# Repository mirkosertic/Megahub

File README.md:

# Megahub

## Introduction

Megahub is an ESP32-based experimentation platform for robotics enthusiasts and makers. It combines native support for LEGO WeDo/Powered Up devices with a web-based IDE featuring Lua scripting and Blockly visual programming. The project is fully open source and ships with hardware schematics, PCB production files, and firmware as a PlatformIO project.

**Build and use it at your own risk.**

---

## Key Features

- **KiCad schematics**: All schematics and PCB production files are available in KiCad and Gerber format
- **WiFi**: Built-in wireless connectivity for remote control and programming
- **Bluetooth**: Acts as a BLE (Bluetooth Low Energy) server and Bluetooth Classic client simultaneously
- **Web IDE**: Configure and program Megahub through the [Megahub IDE](https://mirkosertic.github.io/Megahub/)
- **Visual programming**: Blockly drag-and-drop programming for beginners and rapid prototyping
- **Lua scripting**: Full Lua 5.4 scripting for advanced users
- **SD card storage**: Store multiple projects on an SD card; the IDE remembers which project was last selected for autostart
- **4 LEGO device ports**: Connect up to 4 LEGO WeDo 2.0/Powered Up motors, sensors, and other devices simultaneously
- **IMU**: Integrated MPU6050 6-axis accelerometer and gyroscope for motion sensing
- **FastLED/NeoPixel**: Built-in support for WS2812B addressable RGB LED strips
- **GPIO expansion**: Additional GPIO pins for custom sensors, buttons, and peripherals
- **Gamepad support**: Pair a Bluetooth Classic HID gamepad (e.g., 8BitDo M30) for manual control

---

## Screenshots

**Project management**

**IMU interaction**

**LEGO and Gamepad interaction**

---

## Hardware Photos

---

## Getting Started

### Prerequisites

- [PlatformIO](https://platformio.org/) installed as a CLI tool or as a VSCode extension
- An ESP32 development board
- USB cable for flashing
- Chrome, Edge, or Opera desktop browser (required for the Web Bluetooth API)

### Building the Firmware

1. Clone the repository:
   ```bash
   git clone https://github.com/mirkosertic/Megahub.git
   cd Megahub
   ```

2. Build the project:
   ```bash
   pio run
   ```
   Or click **Build** in the PlatformIO toolbar inside VSCode.

### Flashing the Board

1. Connect the ESP32 board via USB.

2. Flash the firmware:
   ```bash
   pio run --target upload
   ```
   Or click **Upload** in the PlatformIO toolbar inside VSCode.

### First Boot and Connection

The device starts in **Bluetooth mode** by default.

1. Open the [Megahub IDE](https://mirkosertic.github.io/Megahub/) in Chrome, Edge, or Opera on a desktop computer.
2. Click **Connect** in the IDE.
3. Select your Megahub device from the browser's Bluetooth pairing dialog.
4. Once connected, the IDE shows the project list and the logger output.

### Serial Monitor

View diagnostic output from the board:
```bash
pio device monitor
```
Default baud rate: **115200**.

### Testing the IDE Without Hardware

You can run the Megahub IDE locally in your browser without a physical board. This is useful for exploring the interface, building Blockly programs, and inspecting generated Lua code — no firmware flashing required.

```bash
cd frontend
npm install
npm run dev
```

Vite starts a local development server (typically at `http://localhost:5173`). Open that URL in any browser.

**What works in dev mode:**
- Full IDE UI — project management, Blockly workspace, toolbox
- Blockly drag-and-drop programming and real-time Lua code generation
- Lua Preview panel — inspect the generated code for any program

**What does not work:**
- Connecting to a device (no BLE in dev mode)
- Executing or stopping programs — the **Execute** button requires a live connection to the firmware

---

## Hardware Reference

### LEGO Device Ports

Megahub provides **4 LEGO device ports**, numbered **1 to 4**. Each port uses the LEGO Powered Up UART protocol. Two SC16IS752 I2C-to-UART bridge chips translate between the ESP32 and the LEGO connectors: **bridge chip 1** (UART1) drives ports 1 and 2, **bridge chip 2** (UART2) drives ports 3 and 4. Each chip also exposes four additional GPIO pins (GP4–GP7) that can be used for custom sensors or buttons — see `UART1_GP4`–`UART2_GP7` in [LUAAPI.md](LUAAPI.md). All four ports are available from Blockly.

Motor speed range: **-127** (full reverse) to **+127** (full forward). Zero stops the motor.

### GPIO Pins

**FastLED / NeoPixel output** — use any of these GPIO pins for WS2812B LED strips: **13, 16, 17, 25, 26, 27, 32, 33**.

**SD card (SPI bus)**:

| Signal | GPIO |
|--------|------|
| CLK    | 18   |
| MOSI   | 23   |
| MISO   | 19   |
| CS     | 4    |

**IMU (I2C)**: The MPU6050 is connected to the I2C bus. Its address and pins are fixed in hardware.

### Supported LEGO Devices

Megahub supports LEGO WeDo 2.0 and Powered Up devices that communicate over the LEGO Powered Up UART (LUMP) protocol. This includes motors, color and distance sensors, tilt sensors, and other compatible devices. See the [LUMP Protocol Documentation](LUMP.md) for the full technical specification.

---

## Using the IDE

### Connecting

The [Megahub IDE](https://mirkosertic.github.io/Megahub/) runs entirely in your browser and communicates over BLE when the device is in Bluetooth mode.

**Supported browsers**: Chrome, Edge, Opera (desktop only). Firefox and Safari do not support the Web Bluetooth API and cannot connect to the device.

Steps:
1. Open the IDE in a supported browser.
2. Click **Connect**.
3. Select the Megahub device from the pairing dialog.
4. The IDE connects and shows the project list on the left and a logger panel on the right.

### Creating a Project

1. Click **New project** in the project list.
2. Enter a name for the project.
3. The IDE opens the Blockly workspace for that project.

### Programming with Blockly

The Blockly workspace lets you build programs visually without writing code.

1. Find a block in the **toolbox** on the left side of the workspace. Blocks are grouped by category: Control flow, LEGO, Gamepad, FastLED, IMU, I/O, Math, and more.
2. Drag a block onto the canvas and connect it to other blocks.
3. As you build, the IDE generates the corresponding Lua code automatically — expand the **Lua Preview** panel in the sidebar to inspect it.
4. When the program is ready, click **Execute** to send and run it on the device.
5. Output and log messages from the running program appear in the **Logger** panel.

For a visual reference of every available block, see [BLOCKS.md](BLOCKS.md).

### Toolbox Category Guide

The toolbox is divided into these categories:

| Category | What it contains |
|----------|-----------------|
| **Control flow** | `Initialization` block, `Start thread`, `Wait`, `Stop thread` |
| **Logic** | If/else, comparisons (=, ≠, <, >), AND/OR, NOT, boolean values |
| **Loop** | Repeat N times, count-for loop, break/continue |
| **Math** | Arithmetic, rounding, trigonometry, random numbers, constrain |
| **Text** | String operations; **Print to Logger** |
| **Lists** | Create, read, write, sort, and split lists |
| **I/O** | **Set motor speed**, GPIO read/write, pin mode, port selector |
| **LEGO©** | Select sensor mode on a port, read sensor dataset |
| **Gamepad** | Button pressed, analog axis values, connection check |
| **FastLED** | Initialize LED strip, set individual LED colour, show, clear |
| **IMU** | Read yaw, pitch, roll, or acceleration from the on-board sensor |
| **UI** | Display a labelled value in the IDE Logger panel, map visualization (plot position, clear) |
| **Algorithms** | PID controller (init/compute/reset), dead reckoning (init/update/get/reset/set pose), moving average filter, map/scale, hysteresis, debounce, rate limiter, 1D Kalman filter |
| **Debug** | Free heap memory, milliseconds since boot |

> **Common gotcha:** The **Set motor speed** block is in the **I/O** category — not **LEGO©**. The **LEGO©** category only contains sensor blocks (selecting a measurement mode and reading the sensor dataset). If you want to drive a motor, open **I/O**.

### Running and Stopping Programs

- Click **Execute** to upload and start the program.
- Click **Stop** to halt a running program at any time.
- The Logger panel shows output in real time.

### Autostart

You can mark a project as the autostart project. When the IDE connects to the device, it reads the autostart setting and opens that project automatically.

In the IDE project list, find the project you want and toggle the **autostart** switch. This writes the following file to the SD card:

```json
{ "project": "your-project-id" }
```

The file is stored at `/autostart.json` on the SD card. To clear the autostart selection, toggle the switch off in the IDE or delete the file from the SD card.

---

## WiFi Mode

By default Megahub runs in Bluetooth mode. You can switch to WiFi mode to access the web interface over your local network.

### Switching from Bluetooth to WiFi Mode

1. Insert an SD card into the device.
2. Create a file named `config.json` in the root of the SD card with the following content:
   ```json
   {
     "bluetoothEnabled": false,
     "wifiEnabled": true,
     "ssid": "YourNetwork",
     "pwd": "YourPassword"
   }
   ```
3. Reboot the device. It connects to your WiFi network and starts the web server.

You can also run both Bluetooth and WiFi simultaneously by setting both `bluetoothEnabled` and `wifiEnabled` to `true`.

### config.json Reference

| Field              | Type    | Default | Description                        |
|--------------------|---------|---------|------------------------------------|
| `bluetoothEnabled` | boolean | `true`  | Enable BLE and Bluetooth Classic   |
| `wifiEnabled`      | boolean | `false` | Connect to WiFi and start web server |
| `ssid`             | string  | —       | WiFi network name                  |
| `pwd`              | string  | —       | WiFi password                      |

### Accessing the Web UI

Once the device is connected to WiFi:
- Open `http://<device-ip>/` in any browser, **or**
- Open `http://<device-uid>.local/` (requires mDNS support — works on macOS, Linux, and Windows 10+)

The web UI provides the same project management, Blockly programming, and execution features as the Bluetooth-connected IDE. For the full REST API reference used by the web server, see [HUBAPI.md](HUBAPI.md).

---

## Gamepad Support

### Pairing a Gamepad

Scanning and pairing are done from the IDE while the device is connected in Bluetooth mode.

1. Open the **Bluetooth Devices** panel in the IDE sidebar.
2. Click the **Scan** button (circular icon at the top of the panel). The panel shows "Scanning…" while the firmware searches for nearby Bluetooth Classic devices.
3. Put your gamepad into pairing mode so it becomes discoverable.
4. The gamepad appears in the list with its name, MAC address, device type, and signal strength.
5. Click **Pair Device** on the gamepad entry. The firmware initiates pairing; the entry updates to show a **Paired** badge.
6. Once paired, the gamepad state is available to your Blockly programs immediately.

To remove a pairing, click **Remove Pairing** on the paired device entry in the panel.

### Supported Gamepads

Any Bluetooth Classic HID-compatible gamepad should work. The **8BitDo M30** has been tested and confirmed to work.

Gamepad input available in Blockly:

| Input           | Range / Values              |
|-----------------|-----------------------------|
| Buttons (1–16)  | pressed / not pressed       |
| D-pad           | directional state           |
| Left stick X/Y  | -32768 to +32767            |
| Right stick X/Y | -32768 to +32767            |

### Blockly Blocks for Gamepad

The **Gamepad** category in the Blockly toolbox provides 5 blocks for reading button states, D-pad direction, and analog stick values. See [BLOCKS.md](BLOCKS.md) for the full visual reference.

---

## Hardware Features

### LEGO Powered Up

Megahub speaks the LEGO Powered Up UART protocol (LUMP) natively. Each of the 4 ports independently detects a connected device, negotiates its capabilities, and streams sensor data. Motors accept a speed value from -127 to +127. Sensors report values according to the mode you select in your Blockly program.

The **LEGO** category in the Blockly toolbox provides blocks for:
- Selecting a sensor mode on a port
- Reading the current sensor data from a port and dataset

Motor speed is set using the **Set motor speed** block in the **I/O** category.

See [LUMP.md](LUMP.md) for the complete protocol specification.

### FastLED / NeoPixel Addressable LEDs

Connect a WS2812B LED strip to any of the supported GPIO pins (13, 16, 17, 25, 26, 27, 32, or 33). The **FastLED** category in the Blockly toolbox provides 4 blocks for:
- Initializing the LED strip (type, GPIO pin, number of LEDs)
- Setting individual LED colors (RGB)
- Showing/updating the LED strip
- Clearing all LEDs

### IMU — Orientation and Acceleration

The on-board MPU6050 provides 6-axis motion data, updated every 100 ms. Read it in Blockly using the **IMU** block:

| Output          | Unit  | Description                    |
|-----------------|-------|--------------------------------|
| YAW             | °     | Rotation around vertical axis  |
| PITCH           | °     | Forward/back tilt              |
| ROLL            | °     | Left/right tilt                |
| ACCELERATION_X  | m/s²  | Acceleration along X axis      |
| ACCELERATION_Y  | m/s²  | Acceleration along Y axis      |
| ACCELERATION_Z  | m/s²  | Acceleration along Z axis      |

### Algorithm Blocks

The **Algorithms** category provides blocks for closed-loop control and position tracking.

**PID controller:** A proportional-integral-derivative controller for motor speed regulation, line following, or any closed-loop control. Uses an explicit lifecycle:
1. **Init PID** — creates a new controller instance, returns a handle
2. **PID compute** — computes control output using the handle, setpoint, process variable, and gains
3. **PID reset** — clears the state of an existing controller (e.g., when switching setpoints)

Store the handle from `Init PID` in a variable and pass it to `PID compute` in your control loop.

**Dead reckoning (DR):** Estimates the robot's (x, y, heading) pose by integrating wheel encoder ticks and IMU yaw. The following blocks are available:

| Block | Description |
|-------|-------------|
| `Init DR` | Creates a new dead reckoning instance and returns a handle. Call once before your main loop. |
| `DR update` | Updates pose from left/right encoder ticks and IMU yaw. Takes 7 inputs: handle, left ticks, right ticks, yaw (deg), m/tick, wheelbase (m), IMU weight. Does not return a value. |
| `DR pose X/Y/HEADING of` | Reads one component of the pose from a handle — X and Y in meters, HEADING in degrees. |
| `Reset DR pose of` | Resets pose to origin (0, 0, 0°). Re-bootstraps encoder baselines so the next update produces zero delta. |
| `Set DR pose of` | Injects a known (x, y, heading) position for landmark-based drift correction. |

**Moving average filter:** Smooths noisy sensor readings using a sliding window of the last N samples. Uses the same explicit handle pattern as PID and DR — call `Initialize moving average` once before your loop, store the handle in a variable, then pass it to `Moving average` on each update.

| Block | Description |
|-------|-------------|
| `Initialize moving average` | Creates a new moving average filter instance and returns a handle. Store in a variable. Call once before your loop. |
| `Moving average` | Adds a new sample and returns the arithmetic mean of the last N values. Inputs: handle, sensor value, window size (2–50; default 10). On first call the buffer is pre-filled so there is no startup ramp. |

**Map / Scale:** Linearly maps a value from one numeric range to another. Stateless — no initialization required.

| Block | Description |
|-------|-------------|
| `Map` | Maps `value` from `[inMin, inMax]` to `[outMin, outMax]`. Equivalent to Arduino `map()` with float support. Output is not clamped — values outside the input range extrapolate linearly. |

**LEGO motor POS mode prerequisite:** DR reads absolute encoder positions. Before using DR blocks, call `lego select mode` with mode **2** (POS) on the motor ports in `hub.init()`, then wait briefly for the sensor to settle.

For a full explanation including the math, calibration procedure, coordinate conventions, and example programs, see [DEADRECKONING.md](DEADRECKONING.md).

**Signal conditioning filters:** Four filters for cleaning up noisy or jerky signals before they reach your control logic. All use the same explicit handle pattern as PID and DR.

| Block pair | Description |
|-----------|-------------|
| `Initialize hysteresis` + `Hysteresis` | Schmitt trigger — output latches to 0 or 1, only switching when the input crosses a high or low threshold. Eliminates chatter at sensor boundaries. |
| `Initialize debounce` + `Debounce` | Waits for a digital signal to be stable for a minimum number of milliseconds before updating output. Eliminates mechanical button bounce and contact noise. |
| `Initialize rate limiter` + `Rate limit` | Limits how fast the output value can change per call, producing smooth acceleration ramps. Prevents wheel slip and encoder errors from sudden motor commands. |
| `Initialize Kalman filter` + `Kalman filter` | 1D Kalman filter — weighted sensor smoothing based on process noise Q and measurement noise R. More principled than moving average for sensors with known noise characteristics. |

For intuition, math, tuning guidance, and pipeline examples, see [FILTERS.md](FILTERS.md).

### Map Visualization

The IDE sidebar includes a **live map panel** that renders the robot's trail as it moves. Use the **UI** category blocks to drive it:

| Block | Description |
|-------|-------------|
| `Map: plot position` | Sends an (x, y, heading) pose to the map panel. Wire in DR get blocks for x, y, and heading. The firmware rate-limits sends to 5 Hz — call at any rate in your loop. |
| `Map: clear` | Clears the trail from the map panel. Call this at the start of each run alongside `Reset DR pose`. |

### SD Card Storage

Projects created in the IDE are saved to the SD card. The SD card connects over SPI (CLK=18, MOSI=23, MISO=19, CS=4). Use a standard microSD card formatted as FAT32. Configuration files (`config.json`, `autostart.json`) also live in the root of the SD card.

**SD card is required.** If the SD card is absent or fails to mount at boot, the device halts immediately and cannot start.

---

## How Programs Run

Understanding this sequence explains many "why isn't it working?" situations.

### Boot sequence

1. The SD card is mounted. **If mounting fails the device halts** — nothing else starts.
2. `config.json` is read from the SD card root. WiFi and/or Bluetooth are started based on its content.
3. All four LEGO ports initialise and begin device detection in the background.
4. The device enters idle state. No program runs automatically at this point.

> **Autostart does not run a program at boot.** The autostart setting only tells the IDE which project to navigate to when you connect. The device always starts with no program running — you must click **Execute** in the IDE to start a program.

### When you click Execute

1. Any currently running program and all its threads are **stopped immediately**.
2. All four LEGO ports are **reinitialized** (motors stop, sensors reset).
3. A fresh Lua environment is created and the program runs from the top:
   - `hub.init()` — runs synchronously and completes before anything else.
   - `hub.startthread()` — each call spawns a background task that loops independently.
   - The main program body finishes. Background threads continue running.
4. Each thread loops continuously with a 1 ms scheduler yield between iterations.

### When a thread crashes

If a Lua runtime error occurs inside a thread:

- The thread exits and the error appears in the **Logger** panel.
- All four LEGO ports are reinitialized (all motors stop).
- Other threads continue running.

### When you click Stop

1. All threads receive a stop signal and exit.
2. All four LEGO ports are reinitialized (all motors stop, all sensors reset).

**Key point:** every time a program stops — by request, by crashing, or because a new Execute is sent — all motors stop and all ports reset. You never need to manually zero motors before stopping.

---

## Troubleshooting

### BLE Not Connecting

- Make sure you are using Chrome, Edge, or Opera on a **desktop** computer. Mobile browsers and Firefox/Safari do not support the Web Bluetooth API.
- Ensure Bluetooth is enabled on your computer.
- Reload the IDE page and click Connect again — the browser may need a fresh connection attempt.
- Check that no other browser tab or application is already connected to the device (only one BLE connection is active at a time).

### Device Not Found in Bluetooth Scan

- Confirm the device is powered on.
- Move the device closer to your computer — BLE range is typically 5–10 metres in open air.
- Reboot the device and try the scan again.
- If the device was previously paired with a different computer, you may need to remove it from that computer's Bluetooth settings first.

### LEGO Device Not Responding

- Check that the LEGO device cable is fully seated in the port.
- Confirm the port number in your Blockly program matches the physical port (1–4).
- Some LEGO devices require a short delay between commands. Add a **wait** block between motor commands if the device ignores rapid successive commands.
- Reboot the device. The port detection sequence runs on every startup.

### Reading the Serial Log

Connect the device via USB and run:
```bash
pio device monitor
```
The log (115200 baud) shows boot messages, port detection results, BLE connection events, and any errors from running Lua programs. Copy the relevant lines when reporting a bug.

---

## Documentation

| Document | Description |
|----------|-------------|
| [BLOCKS.md](BLOCKS.md) | Complete visual reference for all Blockly blocks, auto-generated with screenshots |
| [LUAAPI.md](LUAAPI.md) | Lua scripting API — all modules, functions, and constants available in Megahub programs |
| [BLEPROTOCOL.md](BLEPROTOCOL.md) | BLE protocol reference — GATT profile, framing, request/response and event formats |
| [HUBAPI.md](HUBAPI.md) | REST API and Server-Sent Events reference for WiFi mode |
| [LUMP.md](LUMP.md) | LEGO Powered Up UART protocol technical specification |
| [MEGAHUBIDE.md](MEGAHUBIDE.md) | Frontend IDE architecture — module structure, state, events, components, testing |
| [DEADRECKONING.md](DEADRECKONING.md) | Dead reckoning guide — intuition, kinematics, math, coordinate conventions, Blockly usage, and calibration |
| [FILTERS.md](FILTERS.md) | Signal conditioning filters guide — hysteresis, debounce, rate limiter, and 1D Kalman filter: intuition, math, tuning, and pipeline patterns |

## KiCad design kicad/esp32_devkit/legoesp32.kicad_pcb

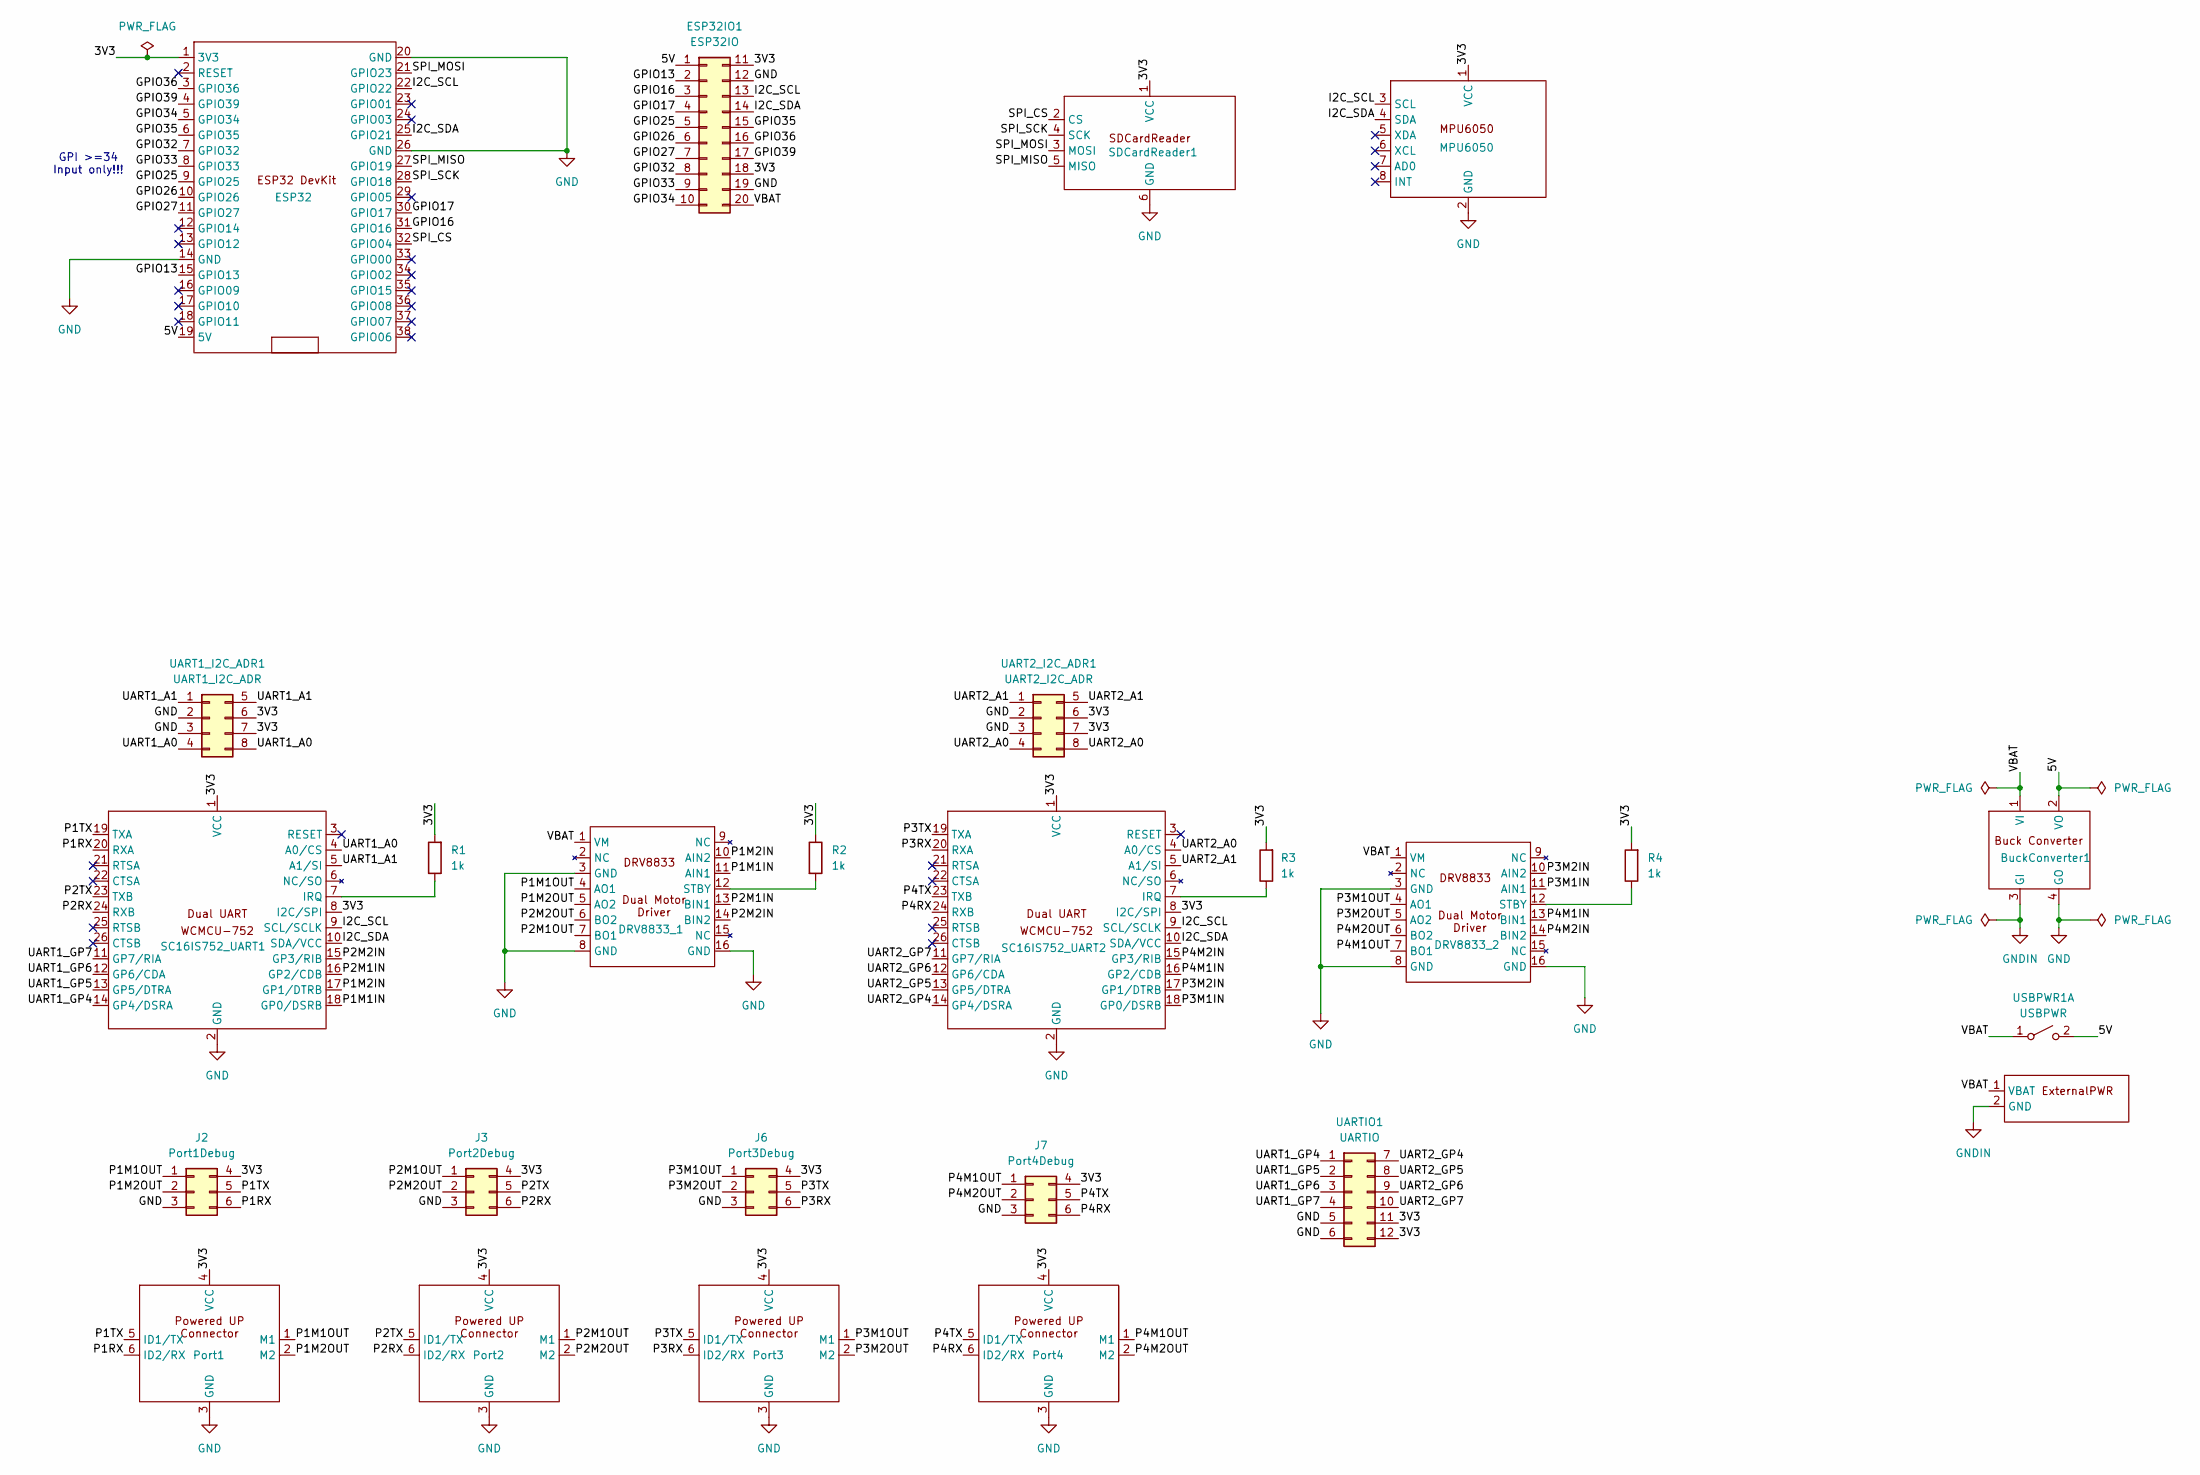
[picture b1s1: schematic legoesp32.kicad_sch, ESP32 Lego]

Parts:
BuckConverter1: BuckConverter
DRV8833_1, DRV8833_2: DRV8833
ESP32: ESP32DevKit
ESP32IO1: ESP32IO; Header_10x2
J2: Port1Debug; Header_3x2
J3: Port2Debug; Header_3x2
J6: Port3Debug; Header_3x2
J7: Port4Debug; Header_3x2
MPU6050: MPU6050
Port1, Port2, Port3, Port4: LegoWedoConnector
R1, R2, R3, R4: 1k; Resistor
SC16IS752_UART1, SC16IS752_UART2: SC16IS752
SDCardReader1: SDCardReader
U1: JST_PH_B2B-PH-K_1x02_P2.00mm_Vertical
UART1_I2C_ADR1: UART1_I2C_ADR; Header_4x2
UART2_I2C_ADR1: UART2_I2C_ADR; Header_4x2
UARTIO1: UARTIO; Header_6x2
USBPWR1: USBPWR; Jumper

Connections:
/3V3: ESP32.1 (3V3), ESP32IO1.11, ESP32IO1.18, J2.4, J3.4, J6.4, J7.4, MPU6050.1 (VCC), Port1.4 (VCC), Port2.4 (VCC), Port3.4 (VCC), Port4.4 (VCC), R1.2, R2.1, R3.2, R4.2, SC16IS752_UART1.1 (VCC), SC16IS752_UART1.8 (I2C/SPI), SC16IS752_UART2.1 (VCC), SC16IS752_UART2.8 (I2C/SPI), SDCardReader1.1 (VCC), UART1_I2C_ADR1.6, UART1_I2C_ADR1.7, UART2_I2C_ADR1.6, UART2_I2C_ADR1.7, UARTIO1.11, UARTIO1.12
/5V: BuckConverter1.2 (VO), ESP32.19 (5V), ESP32IO1.1, USBPWR1.2 (B)
/GPIO13: ESP32.15 (GPIO13), ESP32IO1.2
/GPIO16: ESP32.31 (GPIO16), ESP32IO1.3
/GPIO17: ESP32.30 (GPIO17), ESP32IO1.4
/GPIO25: ESP32.9 (GPIO25), ESP32IO1.5
/GPIO26: ESP32.10 (GPIO26), ESP32IO1.6
/GPIO27: ESP32.11 (GPIO27), ESP32IO1.7
/GPIO32: ESP32.7 (GPIO32), ESP32IO1.8
/GPIO33: ESP32.8 (GPIO33), ESP32IO1.9
/GPIO34: ESP32.5 (GPIO34), ESP32IO1.10
/GPIO35: ESP32.6 (GPIO35), ESP32IO1.15
/GPIO36: ESP32.3 (GPIO36), ESP32IO1.16
/GPIO39: ESP32.4 (GPIO39), ESP32IO1.17
/I2C_SCL: ESP32.22 (GPIO22), ESP32IO1.13, MPU6050.3 (SCL), SC16IS752_UART1.9 (SCL/SCLK), SC16IS752_UART2.9 (SCL/SCLK)
/I2C_SDA: ESP32.25 (GPIO21), ESP32IO1.14, MPU6050.4 (SDA), SC16IS752_UART1.10 (SDA/VCC), SC16IS752_UART2.10 (SDA/VCC)
/P1M1IN: DRV8833_1.11 (AIN1), SC16IS752_UART1.18 (GP0/DSRB)
/P1M1OUT: DRV8833_1.4 (AO1), J2.1, Port1.1 (M1)
/P1M2IN: DRV8833_1.10 (AIN2), SC16IS752_UART1.17 (GP1/DTRB)
/P1M2OUT: DRV8833_1.5 (AO2), J2.2, Port1.2 (M2)
/P1RX: J2.6, Port1.6 (ID2/RX), SC16IS752_UART1.20 (RXA)
/P1TX: J2.5, Port1.5 (ID1/TX), SC16IS752_UART1.19 (TXA)
/P2M1IN: DRV8833_1.13 (BIN1), SC16IS752_UART1.16 (GP2/CDB)
/P2M1OUT: DRV8833_1.7 (BO1), J3.1, Port2.1 (M1)
/P2M2IN: DRV8833_1.14 (BIN2), SC16IS752_UART1.15 (GP3/RIB)
/P2M2OUT: DRV8833_1.6 (BO2), J3.2, Port2.2 (M2)
/P2RX: J3.6, Port2.6 (ID2/RX), SC16IS752_UART1.24 (RXB)
/P2TX: J3.5, Port2.5 (ID1/TX), SC16IS752_UART1.23 (TXB)
/P3M1IN: DRV8833_2.11 (AIN1), SC16IS752_UART2.18 (GP0/DSRB)
/P3M1OUT: DRV8833_2.4 (AO1), J6.1, Port3.1 (M1)
/P3M2IN: DRV8833_2.10 (AIN2), SC16IS752_UART2.17 (GP1/DTRB)
/P3M2OUT: DRV8833_2.5 (AO2), J6.2, Port3.2 (M2)
/P3RX: J6.6, Port3.6 (ID2/RX), SC16IS752_UART2.20 (RXA)
/P3TX: J6.5, Port3.5 (ID1/TX), SC16IS752_UART2.19 (TXA)
/P4M1IN: DRV8833_2.13 (BIN1), SC16IS752_UART2.16 (GP2/CDB)
/P4M1OUT: DRV8833_2.7 (BO1), J7.1, Port4.1 (M1)
/P4M2IN: DRV8833_2.14 (BIN2), SC16IS752_UART2.15 (GP3/RIB)
/P4M2OUT: DRV8833_2.6 (BO2), J7.2, Port4.2 (M2)
/P4RX: J7.6, Port4.6 (ID2/RX), SC16IS752_UART2.24 (RXB)
/P4TX: J7.5, Port4.5 (ID1/TX), SC16IS752_UART2.23 (TXB)
/SPI_CS: ESP32.32 (GPIO04), SDCardReader1.2 (CS)
/SPI_MISO: ESP32.27 (GPIO19), SDCardReader1.5 (MISO)
/SPI_MOSI: ESP32.21 (GPIO23), SDCardReader1.3 (MOSI)
/SPI_SCK: ESP32.28 (GPIO18), SDCardReader1.4 (SCK)
/UART1_A0: SC16IS752_UART1.4 (A0/CS), UART1_I2C_ADR1.4, UART1_I2C_ADR1.8
/UART1_A1: SC16IS752_UART1.5 (A1/SI), UART1_I2C_ADR1.1, UART1_I2C_ADR1.5
/UART1_GP4: SC16IS752_UART1.14 (GP4/DSRA), UARTIO1.1
/UART1_GP5: SC16IS752_UART1.13 (GP5/DTRA), UARTIO1.2
/UART1_GP6: SC16IS752_UART1.12 (GP6/CDA), UARTIO1.3
/UART1_GP7: SC16IS752_UART1.11 (GP7/RIA), UARTIO1.4
/UART2_A0: SC16IS752_UART2.4 (A0/CS), UART2_I2C_ADR1.4, UART2_I2C_ADR1.8
/UART2_A1: SC16IS752_UART2.5 (A1/SI), UART2_I2C_ADR1.1, UART2_I2C_ADR1.5
/UART2_GP4: SC16IS752_UART2.14 (GP4/DSRA), UARTIO1.7
/UART2_GP5: SC16IS752_UART2.13 (GP5/DTRA), UARTIO1.8
/UART2_GP6: SC16IS752_UART2.12 (GP6/CDA), UARTIO1.9
/UART2_GP7: SC16IS752_UART2.11 (GP7/RIA), UARTIO1.10
/VBAT: BuckConverter1.1 (VI), DRV8833_1.1 (VM), DRV8833_2.1 (VM), ESP32IO1.20, U1.1 (VBAT), USBPWR1.1 (A)
GND: BuckConverter1.4 (GO), DRV8833_1.3 (GND), DRV8833_1.8 (GND), DRV8833_1.16 (GND), DRV8833_2.3 (GND), DRV8833_2.8 (GND), DRV8833_2.16 (GND), ESP32.14 (GND), ESP32.20 (GND), ESP32.26 (GND), ESP32IO1.12, ESP32IO1.19, J2.3, J3.3, J6.3, J7.3, MPU6050.2 (GND), Port1.3 (GND), Port2.3 (GND), Port3.3 (GND), Port4.3 (GND), SC16IS752_UART1.2 (GND), SC16IS752_UART2.2 (GND), SDCardReader1.6 (GND), UART1_I2C_ADR1.2, UART1_I2C_ADR1.3, UART2_I2C_ADR1.2, UART2_I2C_ADR1.3, UARTIO1.5, UARTIO1.6
GNDIN: BuckConverter1.3 (GI), U1.2 (GND)
unnamed: DRV8833_1.12 (STBY), R2.2
unnamed: DRV8833_2.12 (STBY), R4.1
unnamed: R1.1, SC16IS752_UART1.7 (IRQ)
unnamed: R3.1, SC16IS752_UART2.7 (IRQ)

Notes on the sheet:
GPI >=34 Input only!!!

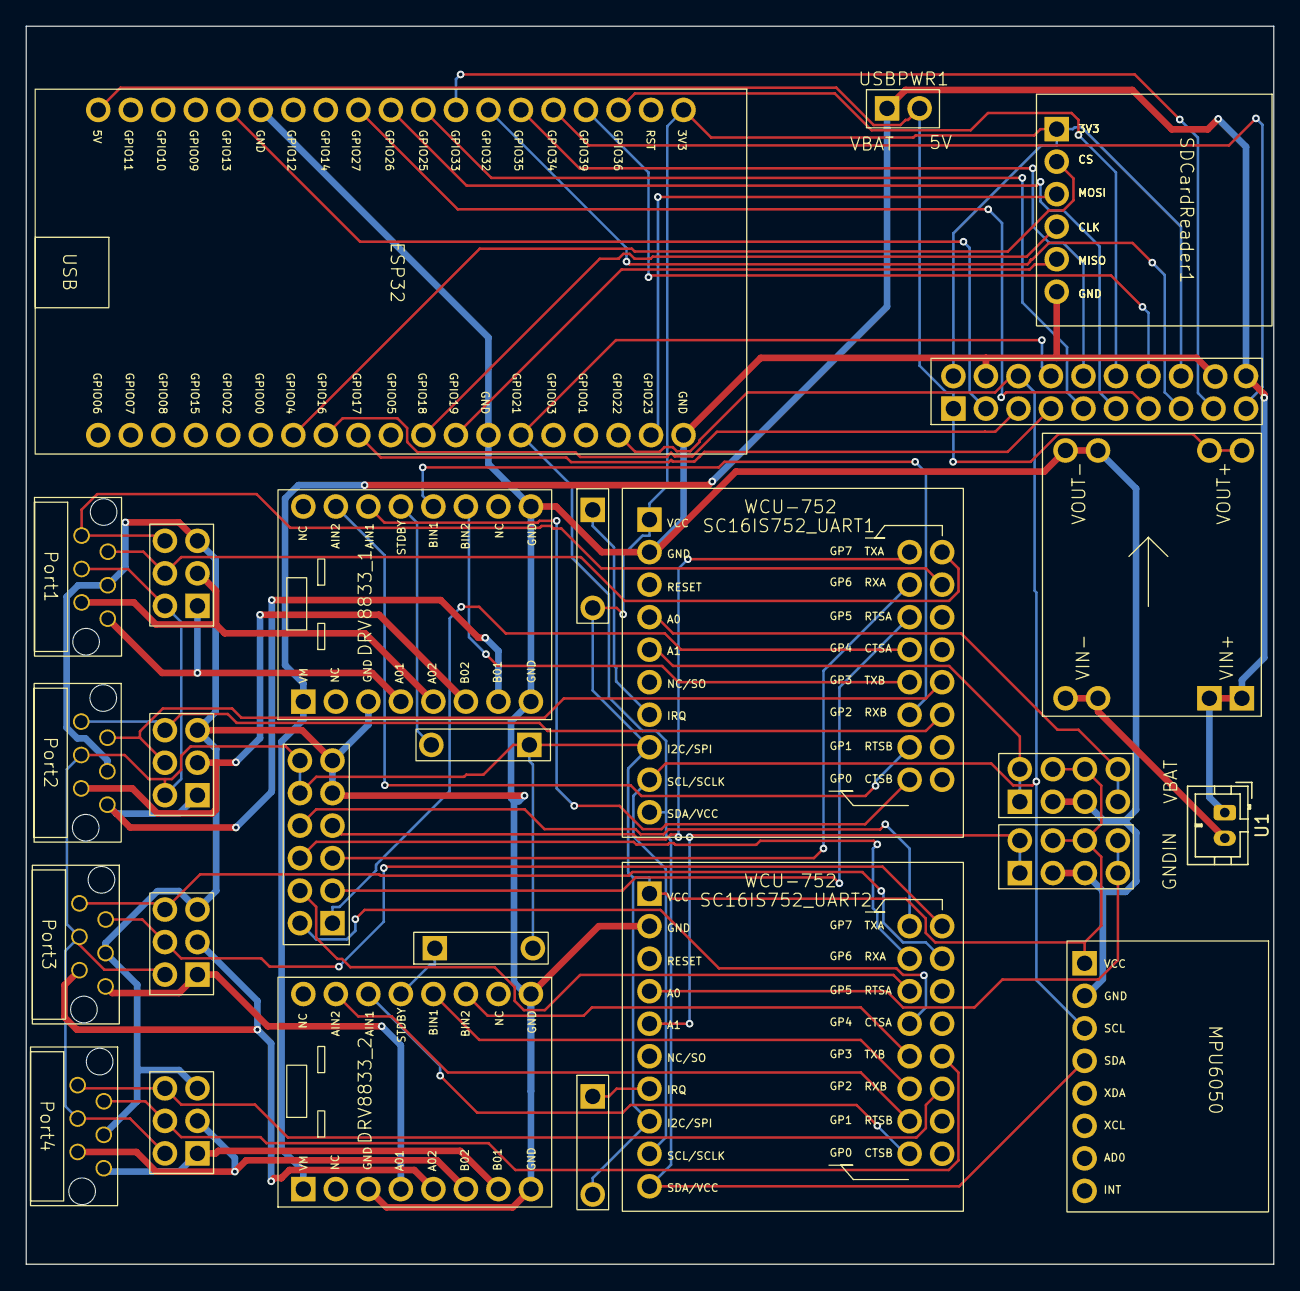
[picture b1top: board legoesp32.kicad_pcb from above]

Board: 2 copper layers, 97.5 x 96.7 mm, 26 parts (0 on the bottom side), 63 nets.

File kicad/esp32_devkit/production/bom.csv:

Designator,Footprint,Quantity,Value,LCSC Part #
BUCKCONVERTER1,BuckConverter,1,~,
"DRV8833_1, DRV8833_2",DRV8833,2,~,
ESP32,ESP32DevKit,1,~,
ESP32IO1,Header_10x2,1,ESP32IO,
J2,Header_3x2,1,Port1Debug,
J3,Header_3x2,1,Port2Debug,
J6,Header_3x2,1,Port3Debug,
J7,Header_3x2,1,Port4Debug,
MPU6050,MPU6050,1,~,
"PORT1, PORT2, PORT3, PORT4",LegoWedoConnector,4,~,
"R1, R2, R3, R4",Resistor,4,1k,
"SC16IS752_UART1, SC16IS752_UART2",SC16IS752,2,~,
SDCARDREADER1,SDCardReader,1,~,
U1,JST_PH_B2B-PH-K_1x02_P2.00mm_Vertical,1,~,
UART1_I2C_ADR1,Header_4x2,1,UART1_I2C_ADR,
UART2_I2C_ADR1,Header_4x2,1,UART2_I2C_ADR,
UARTIO1,Header_6x2,1,UARTIO,
USBPWR1,Jumper,1,USBPWR,

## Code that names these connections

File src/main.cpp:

#include <Arduino.h>

#include "SC16IS752.h"
#include "SC16IS752serialadapter.h"
#include "btremote.h"
#include "commands.h"
#include "configuration.h"
#include "hubwebserver.h"
#include "imu.h"
#include "inputdevices.h"
#include "legodevice.h"
#include "logging.h"
#include "megahub.h"
#include "motorpwmcontroller.h"
#include "portstatus.h"
#include "statusmonitor.h"

#include <FS.h>
#include <SD.h>
#include <SPI.h>
#include <WiFi.h>
#include <Wire.h>
#include <nvs_flash.h>

SC16IS752* i2cuart1 = NULL;
SC16IS752* i2cuart2 = NULL;
IMU* imu = NULL;
Megahub* megahub = NULL;
HubWebServer* webserver = NULL;
Configuration* configuration = NULL;
SerialLoggingOutput* loggingOutput = NULL;
InputDevices* inputDevices = NULL;
BTRemote* btremote = NULL;
MotorPWMController* pwmController = NULL;

#define GPIO_SPI_SS   GPIO_NUM_4
#define GPIO_SPI_SCK  GPIO_NUM_18
#define GPIO_SPI_MOSI GPIO_NUM_23
#define GPIO_SPI_MISO GPIO_NUM_19

void setup() {
	Serial.begin(115200);

	// Initialize logging framework
	loggingOutput = new SerialLoggingOutput(&Serial);
	Logging::instance()->routeLoggingTo(loggingOutput);

	INFO("Setup started");
	INFO("ESP Chip model     : %s", ESP.getChipModel());
	INFO("ESP Chip revision  : %d", ESP.getChipRevision());
	INFO("Running on Arduino : %d.%d.%d", ESP_ARDUINO_VERSION_MAJOR, ESP_ARDUINO_VERSION_MINOR,
	     ESP_ARDUINO_VERSION_PATCH);
	INFO("Running on ESP IDF : %s", esp_get_idf_version());
	INFO("Max  HEAP  is %d", ESP.getHeapSize());
	INFO("Free HEAP  is %d", ESP.getFreeHeap());
	INFO("Max  PSRAM is %d", ESP.getPsramSize());
	INFO("Free PSRAM is %d", ESP.getFreePsram());

	// Force init at this point
	Statusmonitor::instance()->setStatus(BOOTING);
	Commands::instance();
	Portstatus::instance();

	INFO("Initializing SPI bus...");
	SPI.begin(GPIO_SPI_SCK, GPIO_SPI_MISO, GPIO_SPI_MOSI, GPIO_SPI_SS);
	INFO("Mounting SD card...");
	if (!SD.begin(GPIO_SPI_SS)) {
		WARN("Card Mount failed!");
		while (true) {
			Statusmonitor::instance()->setStatus(SD_ERROR);
			vTaskDelay(pdMS_TO_TICKS(50));
		}
	} else {
		uint8_t cardType = SD.cardType();

		if (cardType == CARD_NONE) {
			INFO("No SD card attached");
		} else {
			if (cardType == CARD_MMC) {
				INFO("SD card type MMC");
			} else if (cardType == CARD_SD) {
				INFO("SD card type SDSC");
			} else if (cardType == CARD_SDHC) {
				INFO("SD card type SDHC");
			} else {
				INFO("SD card type UNKNOWN");
			}

			uint64_t cardSize = SD.cardSize() / (1024 * 1024);
			INFO("SD Card Size: %lluMB", cardSize);
		}
	}
	INFO("Free HEAP  is %d", ESP.getFreeHeap());

	INFO("Initializing input decvices registry");
	inputDevices = new InputDevices();

	INFO("Initializing SC16IS752 1 on I2C bus...");
	i2cuart1 = new SC16IS752(SC16IS750_PROTOCOL_I2C, SC16IS750_ADDRESS_AA);
	i2cuart1->begin(2400, 2400);

	INFO("Initializing SC16IS752 2 on I2C bus...");
	i2cuart2 = new SC16IS752(SC16IS750_PROTOCOL_I2C, SC16IS750_ADDRESS_BB);
	i2cuart2->begin(2400, 2400);

	INFO("Initializing Lego Device ports ...");
	SC16IS752SerialAdapter* adapter1 = new SC16IS752SerialAdapter(i2cuart1, CHANNEL_A, 0, 1, SC16IS750_ADDRESS_AA >> 1);
	LegoDevice* legodevice1 = new LegoDevice(adapter1, 0); // Device index 0

	SC16IS752SerialAdapter* adapter2 = new SC16IS752SerialAdapter(i2cuart1, CHANNEL_B, 2, 3, SC16IS750_ADDRESS_AA >> 1);
	LegoDevice* legodevice2 = new LegoDevice(adapter2, 1); // Device index 1

	SC16IS752SerialAdapter* adapter3 = new SC16IS752SerialAdapter(i2cuart2, CHANNEL_A, 0, 1, SC16IS750_ADDRESS_BB >> 1);
	LegoDevice* legodevice3 = new LegoDevice(adapter3, 2); // Device index 2

	SC16IS752SerialAdapter* adapter4 = new SC16IS752SerialAdapter(i2cuart2, CHANNEL_B, 2, 3, SC16IS750_ADDRESS_BB >> 1);
	LegoDevice* legodevice4 = new LegoDevice(adapter4, 3); // Device index 3

	INFO("Creating Motor PWM Controller...");
	pwmController = new MotorPWMController();
	// pwmController->start();

	INFO("Injecting PWM controller into devices...");
	legodevice1->setPWMController(pwmController);
	legodevice2->setPWMController(pwmController);
	legodevice3->setPWMController(pwmController);
	legodevice4->setPWMController(pwmController);
	INFO("Free HEAP  is %d", ESP.getFreeHeap());

	INFO("Initializing IMU");
	imu = new IMU();
	INFO("Free HEAP  is %d", ESP.getFreeHeap());

	INFO("Initializing Megahub...")
	megahub = new Megahub(inputDevices, legodevice1, legodevice2, legodevice3, legodevice4, imu);
	INFO("Free HEAP  is %d", ESP.getFreeHeap());

	INFO("Loading configuration");
	configuration = new Configuration(&SD, megahub);
	configuration->load();
	INFO("Free HEAP  is %d", ESP.getFreeHeap());

	if (configuration->isWiFiEnabled()) {
		configuration->connectToWiFiOrShowConfigPortal();
		// We only reach this point in case there is no configuration needed...
		INFO("Initializing WebServer instance")
		webserver = new HubWebServer(80, &SD, megahub, loggingOutput, configuration);
		INFO("Free HEAP  is %d", ESP.getFreeHeap());
	}

	if (configuration->isBTEnabled()) {
		INFO("Initializing NVS for Bluetooth bonding storage...");
		esp_err_t ret = nvs_flash_init();
		if (ret == ESP_ERR_NVS_NO_FREE_PAGES || ret == ESP_ERR_NVS_NEW_VERSION_FOUND) {
			WARN("NVS partition needs to be erased, erasing...");
			ESP_ERROR_CHECK(nvs_flash_erase());
			ret = nvs_flash_init();
		}
		if (ret != ESP_OK) {
			ERROR("NVS initialization failed: %s", esp_err_to_name(ret));
		} else {
			INFO("NVS initialized successfully");
		}

		INFO("Initializing BT Remote interface")
		btremote = new BTRemote(&SD, inputDevices, megahub, loggingOutput, configuration);
		btremote->begin(megahub->name().c_str());
		INFO("Free HEAP  is %d", ESP.getFreeHeap());
	}

	INFO("Setup completed");
	Statusmonitor::instance()->setStatus(IDLE);

	INFO("Free HEAP  is %d", ESP.getFreeHeap());
	INFO("Free PSRAM is %d", ESP.getFreePsram());
}

void loop() {
	static unsigned long lastHeapLog = 0;
	unsigned long currentMillis = millis();

	// Log free heap memory every 10 seconds
	if (currentMillis - lastHeapLog >= 10000) {
		INFO("Free HEAP: %d bytes, Free PSRAM : %d bytes", ESP.getFreeHeap(), ESP.getFreePsram());

		char task_list_buffer[1024];
		vTaskList(task_list_buffer);
		printf("%s\n", task_list_buffer);

		lastHeapLog = currentMillis;
	}

	if (configuration->isBTEnabled()) {
		btremote->loop();
	}

	megahub->loop();

	if (configuration->isWiFiEnabled()) {
		if (WiFi.status() == WL_CONNECTED) {
			if (!webserver->isStarted()) {
				INFO("Starting WebServer as WiFi status == WL_CONNECTED. Local IP / URL: http://%s:80/",
				     WiFi.localIP().toString().c_str());
				webserver->start();
			} else {
				webserver->loop();
			}
		}
	}
}

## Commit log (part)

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2025-12-29 Fixed logging and UI command
2025-12-29 Optimized logging, added build status badge
2025-12-30 UII cleanup, bug fixing
2026-01-04 Integration testing & bug fixing
2026-01-07 Added some documentation
2026-01-11 Working on BLE API
2026-01-14 Update CI workflow to trigger on main branch only
2026-01-14 Deploying to gh-pages from @ 39dd0124ab9589bc3c36753b80ef1478d8987fe7 🚀
2026-01-14 build.yml löschen
2026-01-14 Fixed asset path
2026-01-14 Added IDE link to README
2026-01-14 Deploying to gh-pages from @ e5f0ee43014017617ecbb2fcbc1ee640fb8ff36c 🚀
2026-01-15 Basis for further refactorings
2026-01-16 Deploying to gh-pages from @ 0e6f2f0a458803c520384208c187cbec68034c7e 🚀
2026-01-17 Deploying to gh-pages from @ 5e0fd9b1b5e0bbc7635f69baa679c5c329b3f608 🚀
2026-01-19 Deploying to gh-pages from @ 6e82eee500639d757cf54fa6472b65da09b1a5a7 🚀
2026-01-20 UI Optimizations / Unified IMU interactions
2026-01-20 Added some files
2026-01-21 Deploying to gh-pages from @ 6ad314deec5018c325464bb7f49b405eb5fd9a38 🚀
2026-01-21 Deploying to gh-pages from @ cbf552b7e5e4e2c41025aca456113ff41e0fe1c3 🚀
2026-01-22 Bug fixing / UI improvements
2026-01-23 Deploying to gh-pages from @ 76e696ff8d401f8d469b34c88f120aa7ca9a56d6 🚀
2026-01-24 Working on documentation
2026-01-25 Deploying to gh-pages from @ 9eec66d5192e31aa6d004e9959bd7b9f01da0da6 🚀
2026-01-26 Deploying to gh-pages from @ 83f93d5d5cbc165cbf8d6ca33b94599c0b8cf445 🚀
2026-01-27 Deploying to gh-pages from @ 2bd8bc7fbd5fd4859447d081ddd78ae36dacde0f 🚀
2026-02-01 Working on better support of Lego combi-modes
2026-02-01 Added context7 rule
2026-02-20 Bug fixing in parsing data frames from LEGO Boost Motor
2026-02-24 Working on LUMP implementation
2026-02-25 Bug fixing
2026-02-27 Bug fixing and documentation updates
2026-02-28 Deploying to gh-pages from @ afc56715f7e77f379924a66e68638bb239f13586 🚀
2026-03-01 Deploying to gh-pages from @ 66844c4b5040c385e4cf165b2c4375bc481c5b6e 🚀
2026-03-01 Added Lua documentation
2026-03-01 Deploying to gh-pages from @ 2c72465f11b4d66eb3dd9cbed92332a74834681c 🚀
2026-03-01 Removed dead code
2026-03-03 Deploying to gh-pages from @ f9b30b48d432eea61d4c548d0ed5382a55a3948d 🚀
2026-03-05 Version updates
2026-03-06 Deploying to gh-pages from @ c890fdfb2af428958dbfdd0dc07b360077aeb539 🚀
2026-03-06 Fixed linter errors
2026-03-06 Testing and bug fixing
2026-03-07 Added support for Kalman, Debouce, Hysteresis and RateLimit blocks
2026-03-07 Working on documentation, added debounce, hysteresis, kalman and rate_limit blocks
2026-03-07 Fixed documentation issues
2026-04-17 Bump flatted from 3.3.3 to 3.4.2 in /frontend
    Bumps [flatted](https://github.com/WebReflection/flatted) from 3.3.3 to 3.4.2.
    - [Commits](https://github.com/WebReflection/flatted/compare/v3.3.3...v3.4.2)
    ---
    updated-dependencies:
    - dependency-name: flatted
    dependency-version: 3.4.2
2026-04-17 Bump happy-dom from 14.12.3 to 20.9.0 in /frontend
    Bumps [happy-dom](https://github.com/capricorn86/happy-dom) from 14.12.3 to 20.9.0.
    - [Release notes](https://github.com/capricorn86/happy-dom/releases)
    - [Commits](https://github.com/capricorn86/happy-dom/compare/v14.12.3...v20.9.0)
    ---
    updated-dependencies:
    - dependency-name: happy-dom
2026-04-17 Bump basic-ftp from 5.1.0 to 5.3.0 in /frontend
    Bumps [basic-ftp](https://github.com/patrickjuchli/basic-ftp) from 5.1.0 to 5.3.0.
    - [Release notes](https://github.com/patrickjuchli/basic-ftp/releases)
    - [Changelog](https://github.com/patrickjuchli/basic-ftp/blob/master/CHANGELOG.md)
    - [Commits](https://github.com/patrickjuchli/basic-ftp/compare/v5.1.0...v5.3.0)
    ---
    updated-dependencies:
2026-04-17 Bump vite and vitest in /frontend
    Bumps [vite](https://github.com/vitejs/vite/tree/HEAD/packages/vite) and [vitest](https://github.com/vitest-dev/vitest/tree/HEAD/packages/vitest). These dependencies needed to be updated together.
    Updates `vite` from 5.4.21 to 8.0.8
    - [Release notes](https://github.com/vitejs/vite/releases)
    - [Changelog](https://github.com/vitejs/vite/blob/main/packages/vite/CHANGELOG.md)
    - [Commits](https://github.com/vitejs/vite/commits/v8.0.8/packages/vite)
    Updates `vitest` from 2.1.9 to 4.1.4
2026-04-18 Configure Dependabot for Maven and npm updates
2026-04-18 Deploying to gh-pages from @ e31a672a96d637ea50d02340c0dd8b1bce849ad5 🚀
2026-04-18 Deploying to gh-pages from @ 8009664531d43949bc9a650b7b79bbe6911f690b 🚀
2026-04-24 Bump vitest from 4.1.4 to 4.1.5 in /frontend
    Bumps [vitest](https://github.com/vitest-dev/vitest/tree/HEAD/packages/vitest) from 4.1.4 to 4.1.5.
    - [Release notes](https://github.com/vitest-dev/vitest/releases)
    - [Commits](https://github.com/vitest-dev/vitest/commits/v4.1.5/packages/vitest)
    ---
    updated-dependencies:
    - dependency-name: vitest
2026-04-24 Bump puppeteer from 24.15.0 to 24.42.0 in /frontend
    Bumps [puppeteer](https://github.com/puppeteer/puppeteer) from 24.15.0 to 24.42.0.
    - [Release notes](https://github.com/puppeteer/puppeteer/releases)
    - [Changelog](https://github.com/puppeteer/puppeteer/blob/main/CHANGELOG.md)
    - [Commits](https://github.com/puppeteer/puppeteer/compare/puppeteer-v24.15.0...puppeteer-v24.42.0)
    ---
    updated-dependencies:
2026-04-24 Bump @blockly/field-colour from 6.0.8 to 6.0.12 in /frontend
    Bumps [@blockly/field-colour](https://github.com/RaspberryPiFoundation/blockly-samples/tree/HEAD/plugins/field-colour) from 6.0.8 to 6.0.12.
    - [Release notes](https://github.com/RaspberryPiFoundation/blockly-samples/releases)
    - [Changelog](https://github.com/RaspberryPiFoundation/blockly-samples/blob/main/plugins/field-colour/CHANGELOG.md)
    - [Commits](https://github.com/RaspberryPiFoundation/blockly-samples/commits/@blockly/field-colour@6.0.12/plugins/field-colour)
    ---
    updated-dependencies:
2026-04-24 Deploying to gh-pages from @ 60e4d3c5dfcd8176b062d857b8ae1e2ba5c71e8d 🚀
2026-04-26 Configure Dependabot for GitHub Actions
    Added configuration for GitHub Actions dependency updates.
2026-04-26 Bump actions/checkout from 4 to 6
    Bumps [actions/checkout](https://github.com/actions/checkout) from 4 to 6.
    - [Release notes](https://github.com/actions/checkout/releases)
    - [Changelog](https://github.com/actions/checkout/blob/main/CHANGELOG.md)
    - [Commits](https://github.com/actions/checkout/compare/v4...v6)
    ---
    updated-dependencies:
2026-04-26 Bump @blockly/workspace-minimap from 0.3.8 to 0.3.9 in /frontend
    Bumps [@blockly/workspace-minimap](https://github.com/RaspberryPiFoundation/blockly-samples/tree/HEAD/plugins/workspace-minimap) from 0.3.8 to 0.3.9.
    - [Release notes](https://github.com/RaspberryPiFoundation/blockly-samples/releases)
    - [Changelog](https://github.com/RaspberryPiFoundation/blockly-samples/blob/main/plugins/workspace-minimap/CHANGELOG.md)
    - [Commits](https://github.com/RaspberryPiFoundation/blockly-samples/commits/@blockly/workspace-minimap@0.3.9/plugins/workspace-minimap)
    ---
    updated-dependencies:
2026-04-26 Bump @blockly/shadow-block-converter from 7.0.9 to 7.0.10 in /frontend
    Bumps [@blockly/shadow-block-converter](https://github.com/RaspberryPiFoundation/blockly-samples/tree/HEAD/plugins/shadow-block-converter) from 7.0.9 to 7.0.10.
    - [Release notes](https://github.com/RaspberryPiFoundation/blockly-samples/releases)
    - [Changelog](https://github.com/RaspberryPiFoundation/blockly-samples/blob/main/plugins/shadow-block-converter/CHANGELOG.md)
    - [Commits](https://github.com/RaspberryPiFoundation/blockly-samples/commits/@blockly/shadow-block-converter@7.0.10/plugins/shadow-block-converter)
    ---
    updated-dependencies:
2026-05-04 Bump globals from 17.5.0 to 17.6.0 in /frontend
    Bumps [globals](https://github.com/sindresorhus/globals) from 17.5.0 to 17.6.0.
    - [Release notes](https://github.com/sindresorhus/globals/releases)
    - [Commits](https://github.com/sindresorhus/globals/compare/v17.5.0...v17.6.0)
    ---
    updated-dependencies:
    - dependency-name: globals
2026-05-07 Bump ip-address from 10.1.0 to 10.2.0 in /frontend
    Bumps [ip-address](https://github.com/beaugunderson/ip-address) from 10.1.0 to 10.2.0.
    - [Commits](https://github.com/beaugunderson/ip-address/commits)
    ---
    updated-dependencies:
    - dependency-name: ip-address
    dependency-version: 10.2.0
2026-05-12 Bump puppeteer from 24.42.0 to 24.43.1 in /frontend
    Bumps [puppeteer](https://github.com/puppeteer/puppeteer) from 24.42.0 to 24.43.1.
    - [Release notes](https://github.com/puppeteer/puppeteer/releases)
    - [Changelog](https://github.com/puppeteer/puppeteer/blob/main/CHANGELOG.md)
    - [Commits](https://github.com/puppeteer/puppeteer/compare/puppeteer-v24.42.0...puppeteer-v24.43.1)
    ---
    updated-dependencies:
2026-05-12 Bump vite from 8.0.11 to 8.0.12 in /frontend
    Bumps [vite](https://github.com/vitejs/vite/tree/HEAD/packages/vite) from 8.0.11 to 8.0.12.
    - [Release notes](https://github.com/vitejs/vite/releases)
    - [Changelog](https://github.com/vitejs/vite/blob/main/packages/vite/CHANGELOG.md)
    - [Commits](https://github.com/vitejs/vite/commits/v8.0.12/packages/vite)
    ---
    updated-dependencies:
2026-05-15 Bump puppeteer from 24.42.0 to 25.0.2 in /frontend
    Bumps [puppeteer](https://github.com/puppeteer/puppeteer) from 24.42.0 to 25.0.2.
    - [Release notes](https://github.com/puppeteer/puppeteer/releases)
    - [Changelog](https://github.com/puppeteer/puppeteer/blob/main/CHANGELOG.md)
    - [Commits](https://github.com/puppeteer/puppeteer/compare/puppeteer-v24.42.0...puppeteer-v25.0.2)
    ---
    updated-dependencies:
2026-05-18 Bump eslint from 10.3.0 to 10.4.0 in /frontend
    Bumps [eslint](https://github.com/eslint/eslint) from 10.3.0 to 10.4.0.
    - [Release notes](https://github.com/eslint/eslint/releases)
    - [Commits](https://github.com/eslint/eslint/compare/v10.3.0...v10.4.0)
    ---
    updated-dependencies:
    - dependency-name: eslint
2026-05-21 Bump vite from 8.0.13 to 8.0.14 in /frontend
    Bumps [vite](https://github.com/vitejs/vite/tree/HEAD/packages/vite) from 8.0.13 to 8.0.14.
    - [Release notes](https://github.com/vitejs/vite/releases)
    - [Changelog](https://github.com/vitejs/vite/blob/main/packages/vite/CHANGELOG.md)
    - [Commits](https://github.com/vitejs/vite/commits/v8.0.14/packages/vite)
    ---
    updated-dependencies:
2026-05-24 Bump ws from 8.20.0 to 8.21.0 in /frontend
    Bumps [ws](https://github.com/websockets/ws) from 8.20.0 to 8.21.0.
    - [Release notes](https://github.com/websockets/ws/releases)
    - [Commits](https://github.com/websockets/ws/compare/8.20.0...8.21.0)
    ---
    updated-dependencies:
    - dependency-name: ws
2026-06-01 Bump vitest from 4.1.7 to 4.1.8 in /frontend
    Bumps [vitest](https://github.com/vitest-dev/vitest/tree/HEAD/packages/vitest) from 4.1.7 to 4.1.8.
    - [Release notes](https://github.com/vitest-dev/vitest/releases)
    - [Changelog](https://github.com/vitest-dev/vitest/blob/main/docs/releases.md)
    - [Commits](https://github.com/vitest-dev/vitest/commits/v4.1.8/packages/vitest)
    ---
    updated-dependencies:
2026-06-01 Bump eslint from 10.4.0 to 10.4.1 in /frontend
    Bumps [eslint](https://github.com/eslint/eslint) from 10.4.0 to 10.4.1.
    - [Release notes](https://github.com/eslint/eslint/releases)
    - [Commits](https://github.com/eslint/eslint/compare/v10.4.0...v10.4.1)
    ---
    updated-dependencies:
    - dependency-name: eslint
2026-06-19 Bump puppeteer from 25.0.2 to 25.1.0 in /frontend
    Bumps [puppeteer](https://github.com/puppeteer/puppeteer) from 25.0.2 to 25.1.0.
    - [Release notes](https://github.com/puppeteer/puppeteer/releases)
    - [Changelog](https://github.com/puppeteer/puppeteer/blob/main/CHANGELOG.md)
    - [Commits](https://github.com/puppeteer/puppeteer/compare/puppeteer-v25.0.2...puppeteer-v25.1.0)
    ---
    updated-dependencies:
2026-06-22 Bump prettier from 3.8.3 to 3.8.4 in /frontend
    Bumps [prettier](https://github.com/prettier/prettier) from 3.8.3 to 3.8.4.
    - [Release notes](https://github.com/prettier/prettier/releases)
    - [Changelog](https://github.com/prettier/prettier/blob/main/CHANGELOG.md)
    - [Commits](https://github.com/prettier/prettier/compare/3.8.3...3.8.4)
    ---
    updated-dependencies:
2026-06-22 Bump happy-dom from 20.9.0 to 20.10.6 in /frontend
    Bumps [happy-dom](https://github.com/capricorn86/happy-dom) from 20.9.0 to 20.10.6.
    - [Release notes](https://github.com/capricorn86/happy-dom/releases)
    - [Commits](https://github.com/capricorn86/happy-dom/compare/v20.9.0...v20.10.6)
    ---
    updated-dependencies:
    - dependency-name: happy-dom
